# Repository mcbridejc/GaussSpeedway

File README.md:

Gauss Speedway
==============

PCB design for the [Gauss Speedway](https://jeffmcbride.net/gauss-speedway/). Designed in Kicad 6.

Demo video: [https://vimeo.com/771275219](https://vimeo.com/771275219)

Firmware: [https://github.com/mcbridejc/speedway-controller](https://github.com/mcbridejc/speedway-controller)

# PCB

The board is a 4-layer board. I typically order it in black soldermask, although this is of course not necessary. I also typically do 1oz inner copper (thinner copper is typically the default) in order to get the trace resistance down. 

# Assembly

The holes in the corners are designed to accomodate M3 screws for mounting. The PCB mounts into a [3D printable frame](./doc/GaussSpeedway_Frame.stl), which has holes to accomodate M3 threaded heat inserts. You can also get by just putting four stand-offs on the corners.

## Cars

The cars can be printed on an FDM printer. I typically use a small 0.2mm nozzle for finer features. You may need to make some adjustments for your printer, the holes for the magnet can be tricky. Ideally, you have enough of a friction fit that the magnets will stay in place while the glue sets, but enough clearance that you can get them in easily. I typically insert them by placing the magnet on the end of a small flat head screw driver, placing a drop of medium CA into the hole, and then press-fit the magnet into the hole. You have to take care to place the magnets in the correct direction.

There are STL files for two car designs in this repo. [This one](./doc/MagnetCar202211.stl) is the better one, with four magnets spaced properly for the guard rails. Just to show some variety, I also put up a [narrow car](./doc/SkinnyCar.stl) with a single row of three magnets. It works as well, all though it is a bit more prone to flying off the track at high velocity.

You can also design your own cars. You just need to maintain the magnet spacing so that all magnets are on the same current direction. It's also pretty important to keep them light; the force created here is pretty small, and if they get too heavy they may just not move, or they may have a harder time staying on the track around a curve. 

# Status 

Rev 3 is tested and seems to be correct.

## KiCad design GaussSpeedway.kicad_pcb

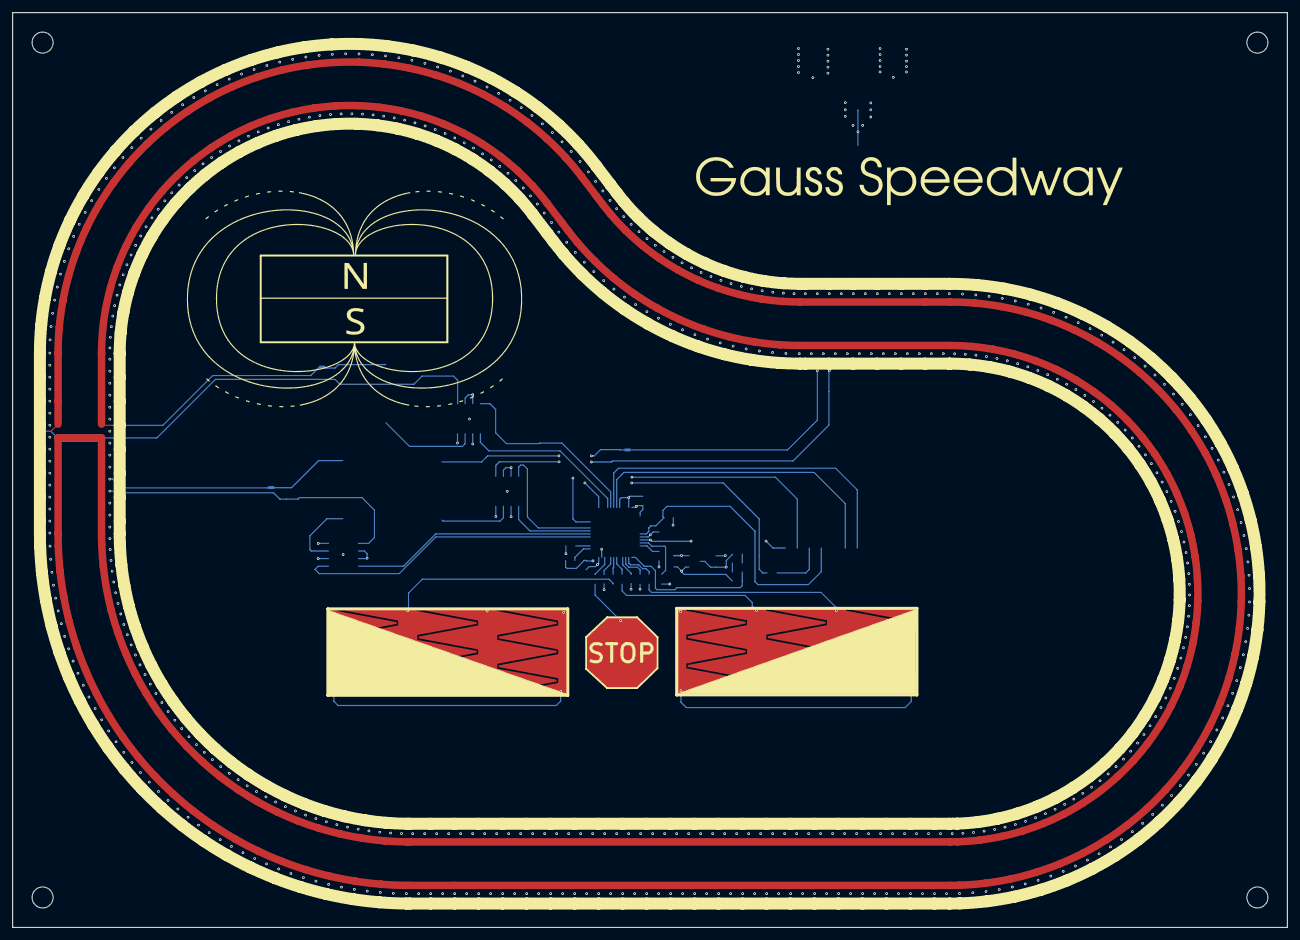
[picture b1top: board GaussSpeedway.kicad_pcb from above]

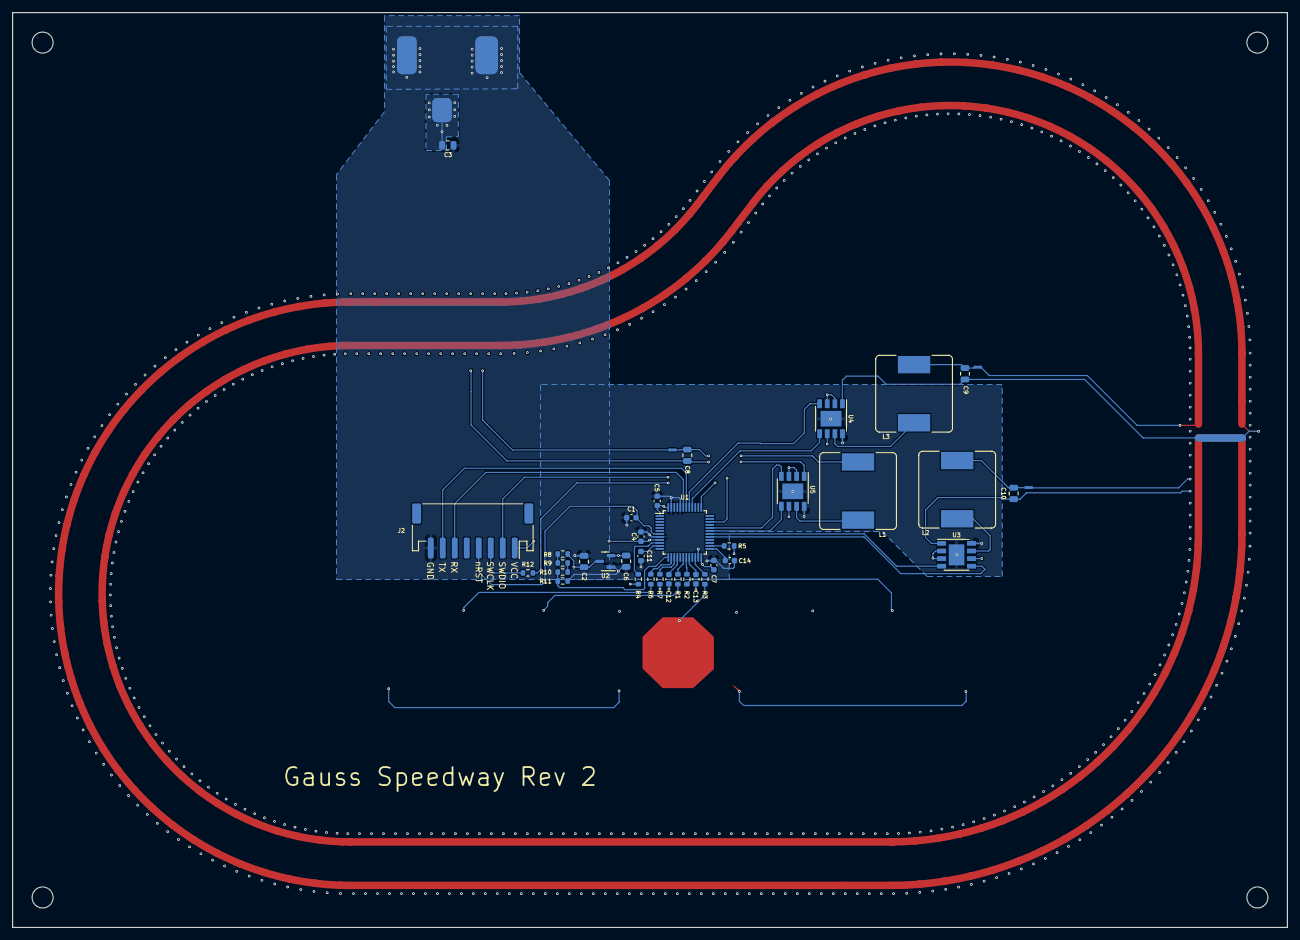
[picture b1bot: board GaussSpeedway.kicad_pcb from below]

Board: 4 copper layers, 212.5 x 152.5 mm, 47 parts (39 on the bottom side), 45 nets.

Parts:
C1, C4, C5, C7: 0.22uF; C_0603_1608Metric
C2, C3, C6, C8, C9, C10: 10uF; C_0805_2012Metric
C11, C12, C13, C14: 47nF; C_0603_1608Metric
G1: Graphic; magnetlogo
H1, H2, H3, H4: MountingHole; MountingHole_3.5mm
J1: Barrel_Jack_Switch; RASM722BK_Barrel
J2: JST PH; JST_PH_S8B-PH-SM4-TB_1x08-1MP_P2.00mm_Horizontal
L1, L2, L3: 68u; L_Bourns_SRR1260
NT1, NT2, NT5: NetTie_2; NetTie-2_SMD_Pad0.5mm
R1, R2, R3, R4, R5, R6, R7, R8, R9, R10, R11, R12: 1k; R_0603_1608Metric
T1, T3: LinearTouch4; linear_touch_40.0mm
T2: Conn_01x01; button
U1: STM32F051C6Tx; LQFP-48_7x7mm_P0.5mm
U2: MCP1754S-3302xCB; SOT-23
U3, U4, U5: ZXBM5210-SP; Diodes_SO-8EP

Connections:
/1A_N: L1.1, U5.7 (OUT2)
/1A_P: C8.1, NT1.2, U5.1 (OUT1)
/1B_N: L2.1, U3.7 (OUT2)
/1B_P: C10.1, NT2.2, U3.1 (OUT1)
/A_IN1: U1.32 (PA11), U5.4 (FWD)
/A_IN2: U1.31 (PA10), U5.5 (REV)
/B_IN1: U1.30 (PA9), U3.4 (FWD)
/B_IN2: U1.29 (PA8), U3.5 (REV)
/FWD1: R5.2, T1.1, T1.4
/FWD2: R7.2, T1.2
/FWD3: R2.1, T1.3
/G1_N: L3.1, U4.7 (OUT2)
/G1_P: C9.1, NT5.2, U4.1 (OUT1)
/G1_SAMPLE: C11.1, U1.11 (PA1)
/G2_SAMPLE: C12.1, U1.16 (PA6)
/G3_SAMPLE: C13.1, U1.20 (PB2)
/G6_SAMPLE: C14.1, U1.25 (PB12)
/G_IN1: U1.41 (PB5), U4.4 (FWD)
/G_IN2: U1.40 (PB4), U4.5 (REV)
/NRST: C1.2, J2.4, U1.7 (NRST)
/REV1: R4.2, T3.1, T3.4
/REV2: R6.2, T3.2
/REV3: R1.1, T3.3
/STOP: R3.1, T2.1
/SWCLK: J2.3, R12.1
/SWDIO: J2.2, U1.34 (PA13)
/UART_RX: J2.6, U1.43 (PB7)
/UART_TX: J2.7, U1.42 (PB6)
/VBUS_SENSE: R10.1, R11.2, U1.13 (PA3)
GND: C1.1, C2.2, C3.2, C4.1, C5.1, C6.2, C7.2, C11.2, C12.2, C13.2, C14.2, J1.2, J1.3, J2.8, R11.1, U1.8 (VSSA), U1.23 (VSS), U1.44 (BOOT0), U1.47 (VSS), U2.1 (GND), U3.8 (GND), U3.9 (GND), U4.8 (GND), U4.9 (GND), U5.8 (GND), U5.9 (GND)
unnamed: C8.2, L1.2, NT1.1
unnamed: C9.2, L3.2, NT5.1
unnamed: C10.2, L2.2, NT2.1
unnamed: R1.2, U1.18 (PB0)
unnamed: R2.2, U1.19 (PB1)
unnamed: R3.2, U1.22 (PB11)
unnamed: R4.1, U1.10 (PA0)
unnamed: R5.1, U1.26 (PB13)
unnamed: R6.1, U1.14 (PA4)
unnamed: R7.1, U1.15 (PA5)
unnamed: R8.1, R9.2
unnamed: R9.1, R10.2
unnamed: R12.2, U1.37 (PA14)
VBUS: C2.1, C3.1, J1.1, R8.2, U2.3 (VI), U3.2 (VM), U3.3 (VDD), U3.6 (VREF), U4.2 (VM), U4.3 (VDD), U4.6 (VREF), U5.2 (VM), U5.3 (VDD), U5.6 (VREF)
VCC: C4.2, C5.2, C6.1, C7.1, J2.1, U1.1 (VBAT), U1.9 (VDDA), U1.24 (VDD), U1.48 (VDD), U2.2 (VO)

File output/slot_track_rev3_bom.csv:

Reference,Value,Footprint,Mfg Part Number,Quantity Per PCB,LCSC,JLCPCB Part #,Comment,Config,Alternates
"C1,C4,C5,C7",0.22uF,C_0603_1608Metric,CL10B224KA8NNNC,4,C21120,C21120,CAP CER 0.22UF 25V X7R 0603,,
"C2,C3,C6,C8,C9,C10",10uF,C_0805_2012Metric,CL21A106KAYNNNG,6,C15850,C15850,CAP CER 10UF 25V X5R 0805,,
"C11,C12,C13,C14",47nF,C_0603_1608Metric,CL10B473KB8WPNC,4,C1622,C1622,CAP CER 0.047UF 50V X7R 0603,,
J1,Barrel_Jack_Switch,RASM722BK_Barrel,RASM722BK,1,,,CONN PWR JACK 2X5.5MM SOLDER,,
J2,JST PH,JST_PH_S8B-PH-SM4-TB_1x08-1MP_P2.00mm_Horizontal,S8B-PH-SM4-TB(LF)(SN),1,C265121,C265121,CONN HEADER SMD R/A 8POS 2MM,,
"L1,L2,L3",68u,L_Bourns_SRR1260,SRR1260A-680M,3,,,FIXED IND 68UH 2.1A 110 MOHM SMD,,
"R1,R2,R3,R4,R5,R6,R7,R8,R9,R10,R11,R12",1k,R_0603_1608Metric,AC0603JR-101KL,12,0603WAF3001T5E,0603WAF3001T5E,RES 1k 0603 +/- 5% 0.1W Thick Film,,
U2,MCP1754S-3302xCB,SOT-23,TPMCP1703T-3302E/CB,1,C3040638,C3040638,IC REG LIN 3.3V 150MA SOT23A-3,,"MCP1754ST-3302E/CB,TPMCP1703T-3302E/CB"
U1,STM32F051C6Tx,LQFP-48_7x7mm_P0.5mm,STM32F051C8T6,1,C9863,C9863,IC MCU 32BIT 32KB FLASH 48LQFP,,
"U3,U4,U5",ZXBM5210-SP,Diodes_SO-8EP,ZXBM5210-SP-13,3,C460767,C460767,IC MOTOR DRIVER 3V-18V 8SO,,

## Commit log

2022-11-04 Rev 1 as ordered
2022-11-18 Rev 2
    - Adjusts track shape
    - Swaps guard rails to top and phase to In1. Hopefully this lowers the
    noise and friction.
    - Adds sample caps
    - Adds SWCLK resistor
    - Adds divider for Vin measurement
2022-11-24 Add readme, STL and image
2022-11-24 Rename project files
2022-11-24 remove fp-info-cache
2022-11-24 Note about being untested
2022-11-29 Add note about rev 2 issues
2023-01-05 Revert an accidental eeschema nightly infection
2023-01-05 Updates for rev 3
    - Expand planes and add vias under hbridge drivers for better thermal
    dissipation
    - Add some thermal dissipation planes on inductor pads
    - Move guard rail current crossover to In2, further from cars and
    closer to the balanced return current on the bottom layer
    - Increase drive trace width from 0.3 to 0.45mm
2023-01-05 Add STLs and update README
2023-01-05 Add notes about 1oz inner copper on PCB
2023-01-05 Replace image with black soldermask rev3
